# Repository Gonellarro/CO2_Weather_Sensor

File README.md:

# README - SENSOR DE CO2

Este documento describe como realizar un dispositivo de bajo costo para registrar la cantidad de CO2 que hay en el aire, indicando mediante un semáforo en que situación nos encontramos. Se incluyen dos versiones de programa en función de si necesitamos solo un avisador de CO2 máximo o si queremos llevar un control de aire, temperatura y humedad más sofisticado y centralizado mediante la consola de Grafana.

----------

TIEMPO ESTIMADO: **120/240 min (básico/avanzado)**

-------

**APRENDERÁS:**

```
IDE ARDUINO, I2C, COMUNICACIÓN SERIE, INCLUSIÓN DE LIBRERÍAS, INCORPORACIÓN DE PLACAS, WIFI, DOCKER, INFLUXDB, TELEGRAPH, GRAFANA, MQTT, SENSORES
```

------

## Visión general

El año 2020 nos sorprendió a todos con la llegada de un virus devastador que ha infectado a todo el mundo sin distinción de raza, sexo o credo. Las fronteras políticas y geográficas han sido meras entelequias humanas que este virus ha despreciado y no le han parado en su expansión. 

La humanidad se ha visto amenazada de forma inesperada y con una rapidez no vista en mucho tiempo. Solo los confinamientos masivos por parte de las naciones han conseguido contener o mitigar el avance del mismo, siendo las otras alternativas, mucho menos efectivas. La dualidad entre el mantenimiento de la economía y la preservación de la salud de la población es el tema que más preocupa a los dirigentes del mundo, ya que este se debate entre salvaguardar nuestra salud o la economía. Muchas de las voces autorizadas del mundo, comparan la reciente situación como mucho peor a la reciente segunda guerra mundial y poder mantener el tejido productivo en marcha sorteando los contagios es el reto que nos tiene en marcha durante el final del 2020 principios del 2021. Hasta que el mundo entero no se inmunice mediante el uso de vacunas o la reversión del virus, tenemos que ser capaces de buscar formas o soluciones que nos ayuden a protegernos y mantener como se pueda la actividad económica. 

Es por eso, que científicos de todo el mundo han considerado la relación entre la ventilación y  la transmisión del virus como una parte fundamental en la expansión del mismo. Un espacio mal o poco ventilado con infectados por el virus es la causa más habitual de contagio. Los aerosoles han aparecido como vectores muy eficaces en la transmisión y es por ello, que para poder controlar estos aerosoles en el aire se apuesta por sensores de CO2 que nos indican, no si existen aerosoles, sino cuan viciado está el aire. La relación entre cantidad de CO2 y dichos aerosoles es directa, con lo cual no es necesario medir niveles de COVID o aerosoles, sino de CO2 y nos aseguraremos un aire limpio sin costes elevados.

Este proyecto trata de obtener lecturas de varios sensores (de CO2, temperatura y humedad) para indicar la calidad del aire en función del CO2. El controlador que se encarga de ello se trata de un Wemos D1 Mini que es un microcontrolador pequeño, barato y con Wifi, que nos permitirá recoger los datos necesarios y enseñarlos mediante un semáforo de colores e incluso, si disponemos de red Wifi, mediante una pequeña página web. El sensor que utilizamos para registrar las ppm (partes por millón) de CO2 es el MHZ19b que hemos comprobado que tiene una fiabilidad y precisión bastante elevada junto con un precio acceptable. El sensor de humedad es el BME280 que también da lecturas de temperatura, pero estas son menos rigurosas. Se tomarán estas últimas de forma cuantitativa y no cualitativa.

El proyecto tiene una segunda parte, más elaborada y compleja, que pretende realizar un sistema de control centralizado de los datos que toma el microcontrolador, usando bases de datos y el sistema gestor de gráficas y dashboards, llamado Grafana. Todo este sistema, se puede instalar sobre un PC, una máquina virtual, una raspberry, etc... pero para hacerlo mucho más modular y portable, se ha optado por hacerlo mediante docker-compose que permite replicarlo con muy poco esfuerzo.

> **Nota:** Sea cual sea el nivel de integración que se quiera llevar a cabo (básico o avanzado), el proyecto se ha pensado para que se pueda llevar a cabo sin cambios. Esto significa que tanto los dispositivos, montaje como código, son los mismos en el nivel básico y el avanzado. Desde un principio se ha pensado en poderlo llevar a cabo sin más pretensión que el nivel básico y no penaliza a aquellos que no quieran complicarse la vida o no necesiten tanto nivel de monitorización

## Dispositivo

El dispositivo básico registrará los datos de CO2, temperatura y humedad de los sensores que incorpora.  Una vez montado el circuito, cargado el programa al Wemos y dado corriente, este empezará con un proceso de precalentado (3 minutos en los que los 3 leds parpadearán de forma secuencial) y se encenderá el led que corresponda al nivel de CO2.

### Componentes necesarios

-  1 x Wemos D1 Mini
-  3 x Resistencias 220 Ohm
-  3 x Led (Rojo, Naranja y Verde)
-  1 x MHZ19B
-  1 x BME 280
-  1 x Protoboard/PCB
-  1 x Cable USB
-  1 x Fuente alimentación 5V/1A

### Diagrama esquemático

### Construir el circuito

A la hora de construir el circuito debemos de tener en cuenta todo el patillaje y como está conectado entre ellos. Es importante tener una descripción detallada de cada componente, así como su DataSheet si es necesario. Veamos ahora el patillaje de cada componente:

- *Wemos D1 mini pinout*

- *MHZ19 pinout*

- *BME280 pinout* 

- *LEDs pinout (recordar que son diodos y por tanto, tienen una pata + y la otra -)*

Procederemos al montaje del circuito en una protoboard, tal y como se muestra en el diagrama esquemático y respetando los pines del diagrama. Hay que conectar el Wemos al ordenador mediante un cable USB, que será el que nos permitirá darle corriente por una parte y cargar el programa por otra.

> **Nota**: Deberemos comprobar en el IDE de Arduino en la sección que viene, que la placa ha sido conectada en un puerto del PC mediante la revisión del puerto. Si no es así, hay que revisar las conexiones con el Wemos, el cable o cambiar de conexión USB del PC, teniendo en cuenta que cada conexión corresponde a un COM diferente.

### Creación del código: Detectar niveles de CO2 con LEDS

1. **Importación de la placa Wemos D1 mini**

Lo primero que debemos hacer al abrir el Arduino IDE es importar los microcontroladores que queremos que sea capaz de compilar. Para ello, añadiremos la linea

```
http://arduino.esp8266.com/stable/package_esp8266com_index.json
```

a las preferencias del IDE/Gestión de URLs adicionales de tarjetas:

Podemos ver que lo hemos importado bien si encontramos la placa LOLIN(WEMOS) D1 R2 & mini en el menú Herramientas\Gestor de tarjetas\ESP8266 Boards (2.7.4) .

Si hemos conectado correctamente el Wemos, lo veremos conecado en el menú Herramientas\Puerto

2. **Importación de las librerías del sensor de CO2**

Debemos bajarnos el ZIP de la librería que está en https://github.com/strange-v/MHZ19 e importarlo como librería. 

Vamos al menú Programa\Incluir Librería\Añadir biblioteca .ZIP

Podemos comprobar que está bien si encontramos la librería en el menú Programa\Incluir Librería\MHZ19

3. **Importación de las librerías del sensor de temperatura**

En este caso es más sencillo, ya que tenemos que añadir solo las librerías de Adafruit y que ya están listadas por defecto. Vamos al menú Programa\Incluir Librería\Administrar bibliotecas y buscamos por BME. Elegimos la librería de Adafruit

Igualmente comprobaremos que lo hemos cargado correctamente si aparece dentro de las librerías disponibles.

4. **El código**

Una vez ya tenemos todo el sistema preparado, podemos cargar el código. Para tener una estructura más clara, legible y escalable, se ha dividido en 5 ficheros diferentes:

- MHZ19B_wemos_BM280.1.3.ino
- Config.h
- Wifi_credentials.h
- CO2_thershold.h
- MQTT.h

El fichero principal, que controla todo el proceso (MHZ19B_wemos_BM280.1.3.ino)

```python
// Wemos MH-Z19B BME28
// Meassure CO2 and environmental data with Wemos D1 mini, MH-Z19B i BME280
//
// Martí Vich, 01/12/2020
//
// based on / credits to:
// https://github.com/AndreasIBZ/ESP32/tree/main/CCS811_BME280_influxDB_Makespace_Mallorca
// https://github.com/miguelangelcasanova/codos
// https://github.com/Makespace-Mallorca/codos

//
// ##### TODO #####
// - Revisión si se puede optimizar el código
// - Revisión del Deep Sleep
// - Mover a libreria parte del código que sea modulable

// #####################################################################################
//
// Code description
// - Measurement of CO2 level and temperature using the MH-Z19B
// - Measurement of the environment (temperature, pressure, humidity) using the BME280
// - Signage of CO2 levels Acceptable, Warning  and Dangerous 
//
// Wiring MH-Z19B -> Wemos D1 mini
// Vin - 5V (VIN)
// RX - GPIO 13 (Software Serial TX) - D8
// TX - GPIO 15 (Software Serial RX) - D7
// GND - GND
//

//
// Wiring BME280 -> Wemos D1 mini
// SCL - D1
// SDA - D2
// VCC - 3V3
// GND - GND

//
// Traffic Light
// GREEN  - D4
// ORANGE - D5
// RED    - D6

// Changelog
// 01/12/2020 - Primera versió 
// 02/12/2020 - Afegim el semàfor i el sensor BME280 
// 03/12/2020 - Revisió rutina d'espera per poder accedir millor al servidor web
//            - Afegit fitxer Wifi_credentials.h
//            - Afegit fitxer CO2_thershold.h
//            - Afegit fitxer Config.h
// 22/12/2020 - Afegit codi MQTT
//            - Revisat codi anterior
//
// #########################################################################################
//
// MH-Z19B
#include <SoftwareSerial.h> // Click here to get the library: http://librarymanager/All#EspSoftwareSerial
#include <MHZ19.h> // library for MH-Z19B: https://github.com/strange-v/MHZ19
#include "CO2_thershold.h" // Límits pels llindars de CO2
#define TXPin 15 // D8 - para MH-Z19B
#define RXPin 13 // D7 - para MH-Z19B

// Instantiate SoftwareSerial
SoftwareSerial ss(RXPin, TXPin);// RX, TX
// Instantiate the MH-Z19B CO2-Sensor with SoftwareSerial
MHZ19 mhz(&ss); 

float CO2;
float Mtemperature;

// BME280
#include <Wire.h>
#include <Adafruit_Sensor.h>
#include <Adafruit_BME280.h>

#define SEALEVELPRESSURE_HPA (1013.25)
// Instantiate the BME sensor with I2C
Adafruit_BME280 bme; 
float Btemperature, Bhumidity, Bpressure, Baltitude;

// WebServer
#include <ESP8266WebServer.h>
#include "WiFi_credentials.h" // credenciales del WiFi
// Instantiate WebServer at port 80
ESP8266WebServer server(80);  

// Traffic Light
int green = 2;   //D4
int yellow = 14; //D5
int red = 12;    //D6

//MQTT
#include <ESP8266WiFi.h>
#include <PubSubClient.h>
#include "MQTT.h" // Confifguració MQTT

//Buffer to decode MQTT messages
char message_buff[100];

long lastMsg = 0;   
long lastRecu = 0;
bool debug = false;  //Display log message if True

WiFiClient espClient;
PubSubClient client(espClient);

// Configuracions generals 
#include "Config.h" // Configuracions generals

// Control del tiempo
long timerCount = 0;

void setup_wifi()
{
  delay(10);
  Serial.println("------------------WIFI---------------");
  Serial.println("Connecting to ");
  Serial.println(WIFI_NAME);

  //connect to your local wi-fi network
  WiFi.begin(WIFI_NAME, WIFI_PASS);

  //check wi-fi is connected to wi-fi network
  while (WiFi.status() != WL_CONNECTED) {
  delay(1000);
  Serial.print(".");
  }
  Serial.println("");
  Serial.println("WiFi connected..!");
  Serial.print("Got IP: ");  Serial.println(WiFi.localIP());

  server.on("/", handle_OnConnect);
  server.onNotFound(handle_NotFound);

  server.begin();
  Serial.println("HTTP server started");
}

void setup()
{
  Serial.begin(115200);
  //WIFI connection
  setup_wifi();

  //MQTT
  client.setServer(mqtt_server, 1883);    // Configure MQTT connexion
    
  //Initialize traffic light
  pinMode(green, OUTPUT);
  pinMode(yellow, OUTPUT);
  pinMode(red, OUTPUT);

  //BME280
  Serial.println("-- Initializing BME280...");
  bme.begin(0x76); 

  // MH-Z19B: Initialize Software Serial
  Serial.println("-- Initializing SoftwareSerial (MH-Z19B)...");
  { ss.begin(9600); 
      delay(100);
      mhz.setAutoCalibration( false );  // default settings - off autocalibration
      Serial.println("Preheating...");
      //Preheating of the sensor (usually 3 minutes)
      for (int i = 0; i<3; i++){
        for (int j = 0; j< int(preheating_Time/(3000)) ; j++){          
          digitalWrite(red, LOW);
          digitalWrite(yellow, LOW);
          digitalWrite(green, LOW);
          delay(int(500));
          if (i==0){
            digitalWrite(red, HIGH);

          }
          if (i==1){
            digitalWrite(red, LOW);  
            digitalWrite(yellow, HIGH);          
         
          }
          if (i==2){
            digitalWrite(red, LOW);  
            digitalWrite(yellow, LOW);   
            digitalWrite(green, HIGH);       
         
          }
          delay(500);          
        }
      }
      Serial.println("-- Reading MH-Z19B --");
      delay(200);
      Serial.print( "Acuracy:" ); 
      Serial.println(mhz.getAccuracy()? "ON" : "OFF" );
      Serial.print( "Detection Range: " ); 
      Serial.println( 5000 );

  }  
}

//Reconnexion MQTT
void reconnect() {
  // Loop until we're reconnected
  int intents = 0;
  while (!client.connected() && intents < 5) {
    Serial.print("Connecting to MQTT broker ...");
    if (client.connect("ESP8266Client", mqtt_user, mqtt_password)) {
      Serial.println("Connected to MQTT Server");
    } else {
      Serial.print("Failed to connect to MQTT server, error : ");
      Serial.print(client.state());
      Serial.println(" Wait 5 secondes before to retry");
      delay(5000);
      intents = intents + 1;
    }
  }
}

void loop()
{
  // Grabbing data from MHZ19B sensor
  MHZ19_RESULT response = mhz.retrieveData();
  if (response == MHZ19_RESULT_OK)
  {
    CO2 = mhz.getCO2();
    Mtemperature = mhz.getTemperature();    
    //Serial.print("MZH19B - ");
    //Serial.print(F("CO2: "));
    //Serial.println(CO2);
    //Serial.print(F("Min CO2: "));
    //Serial.println(mhz.getMinCO2());
    //Serial.print("MZH19B - ");
    //Serial.print(F("Temperature: "));
    //Serial.print(Mtemperature);
    //Serial.print(F("Accuracy: "));
    //Serial.println(mhz.getAccuracy());
  }
  else
  {
    Serial.print(F("MHZ Error, code: "));
    Serial.println(response);
  }
  // Switch CO2
  if (CO2 < CO2_med) {
    digitalWrite(green, HIGH);
    digitalWrite(yellow, LOW);
    digitalWrite(red, LOW);
    
  }
  else{
    if (CO2 > CO2_max) {
       digitalWrite(red, HIGH);
       digitalWrite(yellow, LOW);
       digitalWrite(green, LOW);
    }
    else{
       digitalWrite(yellow, HIGH);
       digitalWrite(green, LOW);
       digitalWrite(red, LOW);
    }    
  }

  // Grabbing data from BME280
  Btemperature = bme.readTemperature();
  Bhumidity = bme.readHumidity();
  Bpressure = bme.readPressure() / 100.0F;
  Baltitude = bme.readAltitude(SEALEVELPRESSURE_HPA);

  //Changin format of data to be sending via Web && MQTT
  String t = String(Btemperature);
  String tM  = String(Mtemperature);
  String h = String(Bhumidity);
  String p = String(Bpressure);
  String a = String(Baltitude);
  String c = String(CO2);

  //Serial.print(F("BME280 - "));
  //Serial.println("Temperature: " + t);

  //MQTT
  if (!client.connected()) {
    reconnect();
  }
  client.loop();    
  delay(500);  

  // Wifi server && MQTT Sending data
  // 1st record the time from the timer
  timerCount = millis();
   while (millis() < timerCount + delay_Time) {
    //Wifi server
    server.handleClient();
    //MQTT
    //Enviam cada minut les messures preses
    if (timerCount - lastMsg > 1000*tMostreig){

      lastMsg = timerCount;
    
      Serial.print("BME280 - ");
      Serial.println("Humidity: " + h);
      Serial.print("MZH19B - ");
      Serial.println("CO2: " + c);
      Serial.println("Temperature: " + tM);
              
      client.publish(String(temperature_topic).c_str(), String(tM).c_str(), true);   // Publish temperature on temperature_topic
      client.publish(String(humidity_topic).c_str(), String(h).c_str(), true);       // and humidity
      client.publish(String(co2_topic).c_str(), String(c).c_str(), true);            // and CO2      
      
    }
    
    //He de revisar que fa això
    //if (now - lastRecu > 100 ) {
    //  lastRecu = now;
    //  client.subscribe("homeassistant/switch1");
    //}

   }

}

void handle_OnConnect() {
  Btemperature = bme.readTemperature();
  Bhumidity = bme.readHumidity();
  Bpressure = bme.readPressure() / 100.0F;
  Baltitude = bme.readAltitude(SEALEVELPRESSURE_HPA);
  int CO2 = mhz.getCO2();
  float Mtemperature = mhz.getTemperature();
  server.send(200, "text/html", SendHTML(Btemperature,Mtemperature,Bhumidity,Bpressure,Baltitude, CO2)); 
  //String t = String(Btemperature);
  Serial.println("Connection done!");
}

void handle_NotFound(){
  server.send(404, "text/plain", "Not found");
}

String SendHTML(float Btemperature,float Mtemperature,float humidity,float pressure,float altitude, int CO2){
  String ptr = "<!DOCTYPE html> <html>\n";
  ptr +="<head><meta name=\"viewport\" content=\"width=device-width, initial-scale=1.0, user-scalable=no\">\n";
  ptr +="<title>ESP8266 Weather Station</title>\n";
  ptr +="<style>html { font-family: Helvetica; display: inline-block; margin: 0px auto; text-align: center;}\n";
  ptr +="body{margin-top: 50px;} h1 {color: #444444;margin: 50px auto 30px;}\n";
  ptr +="p {font-size: 24px;color: #444444;margin-bottom: 10px;}\n";
  ptr +="</style>\n";
  ptr +="</head>\n";
  ptr +="<body>\n";
  ptr +="<div id=\"webpage\">\n";
  ptr +="<h1>ESP8266 Weather Station</h1>\n";
  ptr +="<p>Temperature (BME): ";
  ptr +=Btemperature;
  ptr +="<p>Temperature (MHZ): ";
  ptr +=Mtemperature;  
  ptr +="&deg;C</p>";
  ptr +="<p>Humidity: ";
  ptr +=humidity;
  ptr +="%</p>";
  ptr +="<p>Pressure: ";
  ptr +=pressure;
  ptr +="hPa</p>";
  ptr +="<p>Altitude: ";
  ptr +=altitude;
  ptr +="m</p>";
  ptr +="<p>CO2: ";
  ptr +=CO2;
  ptr +="ppm</p>";
  ptr +="</div>\n";
  ptr +="</body>\n";
  ptr +="</html>\n";
  return ptr;
}
```

Explicación del código paso a paso:

Inicialización del sensor de CO2 (MHZ19B): Este sensor permite la captura de datos mediante transmisión serie. Creamos un objeto de la clase *SoftwareSerial* y lo llamamos *ss*. Le asignamos lis pines 15 y 13 del Wemos para la transmisión y recepción de los datos del sensor. Ver datasheet para más detalles. Creamos un objeto de tipo *MHZ19* llamado *mhz* al cual le asignamos como canal de transmisión serie el objeto que hemos creado *ss*. 

Finalmente, creamos las variables *CO2* y *Mtemperature* que nos guardaran estos valores del sensor.

```python
// MH-Z19B
#include <SoftwareSerial.h> // Click here to get the library: http://librarymanager/All#EspSoftwareSerial
#include <MHZ19.h> // library for MH-Z19B: https://github.com/strange-v/MHZ19
#include "CO2_thershold.h" // Límits pels llindars de CO2
#define TXPin 15 // D8 - para MH-Z19B
#define RXPin 13 // D7 - para MH-Z19B

// Instantiate SoftwareSerial
SoftwareSerial ss(RXPin, TXPin);// RX, TX
// Instantiate the MH-Z19B CO2-Sensor with SoftwareSerial
MHZ19 mhz(&ss); 

float CO2;
float Mtemperature;
```

Veamos ahora el sensor de presión, el BME280. Cargamos las librerías correspondientes para poder interactuar con él y ya lo instanciamos para poder trabajar mediente el protocolo [I2C](https://www.i2c-bus.org/):

```python
// BME280
#include <Wire.h>
#include <Adafruit_Sensor.h>
#include <Adafruit_BME280.h>

#define SEALEVELPRESSURE_HPA (1013.25)
// Instantiate the BME sensor with I2C
Adafruit_BME280 bme; 
float Btemperature, Bhumidity, Bpressure, Baltitude;

```

Seguimos con la creación del servidor web. Para ello cargamos las librerías necesarias, cargamos las credenciales del fichero externo *Wifi_credentials.h* y creamos el objeto *server* en el puerto 80 de tipo *ESP8266Webserver*.

```
// WebServer
#include <ESP8266WebServer.h>
#include "WiFi_credentials.h" // credenciales del WiFi
// Instantiate WebServer at port 80
ESP8266WebServer server(80);  
```

Asignamos los pines 2, 12 y 14 para los leds del semáforo.

```python
// Traffic Light
int green = 2;   //D4
int yellow = 14; //D5
int red = 12;    //D6
```

Finalmente cargamos el módulo MQTT para enviar los mensajes al servidor MQTT. Se crea un cliente de wifi para poder interactuar con el servidor MQTT (espClient) y el objeto client de tipo PubSubClient para publicar las medidas mediante el cliente wifi espClient.

```python
//MQTT
#include <ESP8266WiFi.h>
#include <PubSubClient.h>
#include "MQTT.h" // Confifguració MQTT

//Buffer to decode MQTT messages
char message_buff[100];

long lastMsg = 0;   
long lastRecu = 0;
bool debug = false;  //Display log message if True

WiFiClient espClient;
PubSubClient client(espClient);
```

Creamos la función de setup de la Wifi. Mostramos por el monitor serie cual esla  IP que le ha dado el servidor de DHCP. Si queremos que use una IP estática hay que cambiar esta parte del código.

También arranca el servidor web cuando ya tiene IP.

```python
void setup_wifi()
{
  delay(10);
  Serial.println("------------------WIFI---------------");
  Serial.println("Connecting to ");
  Serial.println(WIFI_NAME);

  //connect to your local wi-fi network
  WiFi.begin(WIFI_NAME, WIFI_PASS);

  //check wi-fi is connected to wi-fi network
  while (WiFi.status() != WL_CONNECTED) {
  delay(1000);
  Serial.print(".");
  }
  Serial.println("");
  Serial.println("WiFi connected..!");
  Serial.print("Got IP: ");  Serial.println(WiFi.localIP());

  server.on("/", handle_OnConnect);
  server.onNotFound(handle_NotFound);

  server.begin();
  Serial.println("HTTP server started");
}
```

Analizamos el setup más despacio para revisar que hace cada parte:

1. Indicamos la velocidad de conexión, arrancamos la wifi, configuramos el cliente de MQTT con la dirección del servidor y el puerto, así como indicamos que los pines verde, naranja y rojo son de salida

```python
  Serial.begin(115200);
  //WIFI connection
  setup_wifi();

  //MQTT
  client.setServer(mqtt_server, 1883);    // Configure MQTT connexion
    
  //Initialize traffic light
  pinMode(green, OUTPUT);
  pinMode(yellow, OUTPUT);
  pinMode(red, OUTPUT);
```

2. Arrancamos la comunicación I2C con el BME280. Su dirección es la 0x76 (consultar datasheet)
3. Arrancamos la comunicación serie con el MHZ19B. Establecemos la velocidad de comunicación a 9600 baudios, realizamos el preheating como indican en el datasheet indicando mediante el parpadeo de los leds, que estamos precalentando el sensor. Van parpadeando uno a uno, durante un minuto, hasta que pasan los 3 minutos.

```python
  //BME280
  Serial.println("-- Initializing BME280...");
  bme.begin(0x76); 

  // MH-Z19B: Initialize Software Serial
  Serial.println("-- Initializing SoftwareSerial (MH-Z19B)...");
  { ss.begin(9600); 
      delay(100);
      mhz.setAutoCalibration( false );  // default settings - off autocalibration
      Serial.println("Preheating...");
      //Preheating of the sensor (usually 3 minutes)
      for (int i = 0; i<3; i++){
        for (int j = 0; j< int(preheating_Time/(3000)) ; j++){          
          digitalWrite(red, LOW);
          digitalWrite(yellow, LOW);
          digitalWrite(green, LOW);
          delay(int(500));
          if (i==0){
            digitalWrite(red, HIGH);          
      	  }
      	if (i==1){
        	digitalWrite(red, LOW);  
        	digitalWrite(yellow, HIGH);          
      	}
      	if (i==2){
        	digitalWrite(red, LOW);  
        	digitalWrite(yellow, LOW);   
        	digitalWrite(green, HIGH);            
      	}
      	delay(500);          
    	}
  	}
 	Serial.println("-- Reading MH-Z19B --");
  	delay(200);
  	Serial.print( "Acuracy:" ); 
  	Serial.println(mhz.getAccuracy()? "ON" : "OFF" );
  	Serial.print( "Detection Range: " ); 
  	Serial.println( 5000 );
```

Finalmente analizamos el loop, como parte más interesante de la práctica. 

1. Recogemos los datos de MHZ19B

```python
  // Grabbing data from MHZ19B sensor
  MHZ19_RESULT response = mhz.retrieveData();
  if (response == MHZ19_RESULT_OK)
  {
    CO2 = mhz.getCO2();
    Mtemperature = mhz.getTemperature();    
  }
  else
  {
    Serial.print(F("MHZ Error, code: "));
    Serial.println(response);
  }

```

2. Encendemos el led que toca en función del valor de CO2 obtenido. En este caso hemos optado por usar una secuencia de ifs anidados, pero se puede programar mediante la sentencia [switch...case](https://www.arduino.cc/reference/en/language/structure/control-structure/switchcase/)

```python
 // Switch CO2
  if (CO2 < CO2_med) {
    digitalWrite(green, HIGH);
    digitalWrite(yellow, LOW);
    digitalWrite(red, LOW);
    
  }
  else{
    if (CO2 > CO2_max) {
       digitalWrite(red, HIGH);
       digitalWrite(yellow, LOW);
       digitalWrite(green, LOW);
    }
    else{
       digitalWrite(yellow, HIGH);
       digitalWrite(green, LOW);
       digitalWrite(red, LOW);
    }    
  }

```

3. Recogemos los datos del BME280

```python
  // Grabbing data from BME280
  Btemperature = bme.readTemperature();
  Bhumidity = bme.readHumidity();
  Bpressure = bme.readPressure() / 100.0F;
  Baltitude = bme.readAltitude(SEALEVELPRESSURE_HPA);
```

4. Enviamos los datos por MQTT y lo publicamos al servidor web del Wemos

   Cada delay_time revisamos los datos

   ```python
     // Wifi server && MQTT Sending data
     // 1st record the time from the timer
     timerCount = millis();
      while (millis() < timerCount + delay_Time) {
   ```

   Atendemos el servicio web

   ```python
   //Wifi server
   server.handleClient();
   ```

   Cada minuto enviamos los datos al servicio de MQTT
   
   ```python
       //Enviam cada minut les messures preses
       if (timerCount - lastMsg > 1000*tMostreig){
   
       lastMsg = timerCount;
       
       Serial.print("BME280 - ");
       Serial.println("Humidity: " + h);
       Serial.print("MZH19B - ");
       Serial.println("CO2: " + c);
       Serial.println("Temperature: " + tM);
       
       client.publish(String(temperature_topic).c_str(), String(tM).c_str(), true);   // Publish temperature on temperature_topic
       client.publish(String(humidity_topic).c_str(), String(h).c_str(), true);       // and humidity
       client.publish(String(co2_topic).c_str(), String(c).c_str(), true);            // and CO2          
       }
   ```

El resto del código no es tan imprescindible para entender el funcionamiento del sensor y materializa lo que le hemos programado en lo explicado hasta aquí.

Revisamos el resto de ficheros:

Disponemos de un fichero de configuración general (config.h), que controla:

- Tiempo de preheating
- Tiempo de recarga de sensores
- Tiempo de muestreo de MQTT

```python
#ifndef Config_h

// General configuration parameters

const int delay_Time = 15000; // 15 seconds
const int preheating_Time = 180000; // 3 minutes
const int tMostreig = 15; // 60 seconds to send every meassurement to MQTT server

#endif  
```

Disponemos de un fichero (Wifi_credentials.h) que configura los parámetros de la wifi:

```python
#ifndef WiFi_credentials_h

// WiFi
const char WIFI_NAME[] = "your_ISD";
const char WIFI_PASS[] = "your_pass";

#endif
```

Disponemos de un fichero (CO2_thershold.h) que configura los umbrales de encendido de los leds:

```python
#ifndef CO2_thershold_h

// WiFi
const int CO2_med = 599;
const int CO2_max = 799;

#endif
```

Finalmente, disponemos de un fichero (MQTT.h) que configura los parámetros de los meassurements/topics que se envían mediante MQTT a la base de datos InfluxDB para visualizarlos en Grafana. Sin duda este es el fichero más extraño y no es necesario rellenar si no se van a usar los datos en un sistema centralizado.

```python
const char mqtt_server[] = "";   // MQTT Server IP address
const char mqtt_user[] = "";                // if exist
const char mqtt_password[] = "";            // idem

String device_name = "";

String temperature_topic = "sensors/" + device_name + "/temperature";  //Topic temperature
String humidity_topic = "sensors/" + device_name + "/humidity";        //Topic humidity
String co2_topic = "sensors/" + device_name + "/co2";                  //Topic CO2
```

### Pruebas y funcionamiento

Pasaremos ahora a cargar el código al Wemos. Para ello, una vez conectado el Wemos y confirmado que el IDE de Arduino lo detecta en algún puerto del PC, le daremos a compilar y subir.

Si todo ha ido bien, el programa se habrá compilado y se habrá subido al Wemos. Entonces veremos la secuencia de LEDs:

1. Led verde encendido: Búsqueda de Wifi y asignación de IP
2. Ciclo de encendido/apagado de cada uno de los leds durante un minuto, para precalentar el sensor de CO2 (primero el rojo, luego el naranja y finalmente el verde)
3. Finalemente se encenderá el Led correspondiente al nivel que le hayamos programado en el fichero de configuración.
4. Podemos acceder al dispositivo mediante Wifi a la dirección IP del mismo

//IMATGE

### BONUS: Creación de la placa PCB

Si queremos hacer el proyecto redondo, ya solo nos queda pasar todo el montaje a una placa. Podemos optar por las placas perforadas y cablear todos los componentes, o diseñar una placa desde cero y enviarla a fabricar. 

En este caso ya hemos realizado la placa, la hemos diseñado con [Kicad](https://kicad.org/) y enviado a fabricar a un proveedor de Internet. Dejamos los ficheros necesarios (JLCPCB.zip) en la carpeta  *Dessign/Kicad* para que se puedan enviar al proveedor que se desee y poder acabar el dispositivo de forma que se pueda usar en la vida real.

El dispositivo montado

--------

## Monitorización

Ya tenemos el dispositivo montado y funcionando. Ahora queremos poder monitorizar de forma centralizada los datos que registra: CO2, temperatura, humedad y presión. Si bien hay que hacer notar, los datos de la concentración de CO2 parecen bastante reales y acertados, tanto los de temperatura como de presión salen fuera de margen y solo se pueden tomar de forma cuantitativa y no cualitativa.

Ejemplo de dashboard de monitorización, que es a lo que aspiramos en este punto:

### Arquitectura

---------

- Por una parte, el dispositivo tiene la capacidad de poder conectarse a una red IP mediante WIFI pero debemos evitar que se pueda conectar con Internet. <u>Solamente debe de ser accesible dentro de la red local</u>. Esto lo hace más seguro y  tenemos el sistema menos expuesto a posibles ataques externos. Por tanto, pongo como premisa que el dispositivo (Wemos D1 mini) no esté conectado a una red externa. Esto no tiene que ver que no se pueda monitorizar desde el exterior, ojo. Lo que hay que evitar a toda costa es que nuestro dispositivo pueda ser accesible.

- Los datos obtenidos deben de incorporarse en una base de datos local para poderlos gestionar de una forma adecuada.

- Mediante un navegador web accedemos a la base de datos y obtenemos las gráficas que la aplicación web que elijamos nos muestre desde nuestra red local.

  > **Nota**: Si queremos que sea accesible desde Internet, podemos poner un proxy reverso, pero no es el objetivo de esta práctica. Si se quiere realizar, recomendamos el docker *jwilder/nginx-proxy*.

Una vez clara cual va a ser la arquitectura, debemos elegir que componentes usar. Debe de quedar claro que esta es una posible elección y que el mercado ofrece muchas soluciones tanto gratuitas como de pago y no necesariamente deberíamos hacerlo así. Es simplemente la que nos ha parecido que cubría mejor las necesidades del proyecto. 

- **Máquina usada:** Máquina Virtual Ubuntu Server 20.04 (2GB de RAM, Core i3 7100) pero se puede usar una raspberry pi, una máquina dedicada o un servicio cloud
- **Container:** docker-compose. 
- **Servicio de monitorización:**  Grafana
- **Base de datos:** InfluxDB
- **Listener:**
  - Mosquito MQTT
  - Telegraf

A esta configuración se le conoce como el stack TIG (Telegraf, InfluxDB y Grafana) con lo que encontraremos bastante información en Internet sobre ello si queremos indagar un poco más. El funcionamiento práctico es el siguiente:

*Fuente: https://hackmd.io/@lnu-iot/tig-stack*

Si juntamos MQTT con mosquito y TIG: 

*Fuente: https://dzone.com/articles/raspberry-pi-iot-sensors-influxdb-mqtt-and-grafana*

#### Instalación

----------------

1. **Instalar docker**: Ver [documentación](https://docs.docker.com/engine/install/ubuntu/) de docker para Ubuntu. En la misma página encontraremos como instalarlo en otros sistemas operativos.

   ***Resumen de comandos:***

   Actualizamos y confirmamos que tenemos todos los paquetes para poder usar apt sobre un repositorio HTTPS:

   ```bash
   $ sudo apt-get update
   
   $ sudo apt-get install \
       apt-transport-https \
       ca-certificates \
       curl \
       gnupg-agent \
       software-properties-common
   ```

   Añadimos la clave GPG oficial de Docker:

   ```bash
   $ curl -fsSL https://download.docker.com/linux/ubuntu/gpg | sudo apt-key add -
   ```

   Añadimos el repositorio **estable**

   ```bash
   $ sudo add-apt-repository \
      "deb [arch=amd64] https://download.docker.com/linux/ubuntu \
      $(lsb_release -cs) \
      stable"
   ```

   Finalmente instalamos el motor de Docker:

   ```bash
    $ sudo apt-get update
    $ sudo apt-get install docker-ce docker-ce-cli containerd.io
   ```

   Verificamos que la instalación de Docker Engine está funcionando correctamente arrancando la imagen *hello-world*

   ```bash
   $ sudo docker run hello-world
   ```

   Si va bien, nos saldrá una pantalla como esta:

2. **Instalar docker-compose:** Para ello seguimos la documentación oficial de docker que podemos encontrar [aquí](https://docs.docker.com/compose/install/). Aunque está alojada en Github, la misma página de docker tiene un manual muy completo y es el que hemos seguido.

   ***Resumen de comandos:***

   Descarga de la última versión estable de docker-compose:

   ```bash
   sudo curl -L "https://github.com/docker/compose/releases/download/1.28.2/docker-compose-$(uname -s)-$(uname -m)" -o /usr/local/bin/docker-compose
   ```

   Añadimos los permisos de ejecución al binario:

   ```bash
   sudo chmod +x /usr/local/bin/docker-compose
   ```

   Comprobamos que la instalación ha sido correcta ejecutando el comando:

   ```bash
   docker-compose --version
   ```

   Si ha ido bien debemos obtener un mensaje como este:

#### Configuración

------------

Ahora ya tenemos la base instalada para poder correr los servicios necesarios. Repasemos el montaje:

**MQTT:** El dispositivo debe enviar las medidas mediante un cliente MQTT a un servidor MQTT.  Debe de estar configurado tanto para recibir los datos del dispositivo como para enviarlos a la base de datos. Veamos quedaría en la configuración de *docker-compose*:

```yaml
  mqtt:
    container_name: mqtt
    image: eclipse-mosquitto:latest
    networks:
      - tig_net    
    ports:
      - "1883:1883"
      - "9001:9001"
    user: "0"
    volumes:
      - mosquitto_volume:/mosquitto
    restart: always
```

***Puntos importantes***

```
- puertos de escucha de los dispositivos: 1883
- puerto de escucha web: 9001
- definimos la red para este stack
```

*Info de la imagen: https://hub.docker.com/_/eclipse-mosquitto*

**TELEGRAF:** El servidor MQTT no es capaz de transferir los datos directamente a la base de datos y necesita un servicio de escucha que los pase en el formato correcto de la base de datos elegida, en este caso, InfluxDB. El programa para traducirlo es el Telegraf. Su configuración se divide en 2 partes: *docker-compose* y un fichero de configuración (Telegraf sirve para recolectar información de muy diversas fuentes y consolidarlas a otras muy diversas bases de datos/componentes). 

docker-compose:

```yaml
  telegraf:
    container_name: telegraf
    image: telegraf
    networks:
      - tig_net    
    volumes:
      - ./tig/config/telegraf:/etc/telegraf:ro
      - /var/run/docker.sock:/var/run/docker.sock
    restart: always
    depends_on:
      - influxdb
      - mqtt
```

Fichero de configuración: Este fichero hay que crearlo y guardarlo en la ubicación *dc_tig/tig/conf/telegraf/telegraf.conf* :

*Parte MQTT*

```bash
 [[inputs.mqtt_consumer]]
#   ## Broker URLs for the MQTT server or cluster.  To connect to multiple
#   ## clusters or standalone servers, use a seperate plugin instance.
#   ##   example: servers = ["tcp://localhost:1883"]
#   ##            servers = ["ssl://localhost:1883"]
#   ##            servers = ["ws://localhost:1883"]
   servers = ["tcp://mqtt:1883"]
#
#   ## Topics that will be subscribed to.
   topics = [
     "telegraf/host01/cpu",
     "telegraf/+/mem",
     "sensors/#"
   ]
#
#   ## The message topic will be stored in a tag specified by this value.  If set
#   ## to the empty string no topic tag will be created.
#   # topic_tag = "topic"
#
#   ## QoS policy for messages
#   ##   0 = at most once
#   ##   1 = at least once
#   ##   2 = exactly once
#   ##
#   ## When using a QoS of 1 or 2, you should enable persistent_session to allow
#   ## resuming unacknowledged messages.
    qos = 0
#
#   ## Connection timeout for initial connection in seconds
#   # connection_timeout = "30s"
#
#   ## Maximum messages to read from the broker that have not been written by an
#   ## output.  For best throughput set based on the number of metrics within
#   ## each message and the size of the output's metric_batch_size.
#   ##
#   ## For example, if each message from the queue contains 10 metrics and the
#   ## output metric_batch_size is 1000, setting this to 100 will ensure that a
#   ## full batch is collected and the write is triggered immediately without
#   ## waiting until the next flush_interval.
#   # max_undelivered_messages = 1000
#
#   ## Persistent session disables clearing of the client session on connection.
#   ## In order for this option to work you must also set client_id to identify
#   ## the client.  To receive messages that arrived while the client is offline,
#   ## also set the qos option to 1 or 2 and don't forget to also set the QoS when
#   ## publishing.
#   # persistent_session = false
#
#   ## If unset, a random client ID will be generated.
#   # client_id = ""
#
#   ## Username and password to connect MQTT server.
    username = "telegraf"
    password = "telegraf"
#
#   ## Optional TLS Config
#   # tls_ca = "/etc/telegraf/ca.pem"
#   # tls_cert = "/etc/telegraf/cert.pem"
#   # tls_key = "/etc/telegraf/key.pem"
#   ## Use TLS but skip chain & host verification
#   # insecure_skip_verify = false
#
#   ## Data format to consume.
#   ## Each data format has its own unique set of configuration options, read
#   ## more about them here:
#   ## https://github.com/influxdata/telegraf/blob/master/docs/DATA_FORMATS_INPUT.md
    #data_format = "influx"
    data_format = "value"
    data_type = "float"
```

***Puntos importantes:***

```
- servidor:  tcp://mqtt:1883. Hay que tener en cuenta que el servicio de docker-compose crea una red privada con los nombres de los "servicios" definidos en el fichero yml. El nombre que le pongamos al servicio de mqtt debe de ser el que pongamos aquí como servidor. 

- topics: aquí hay que definir los topics que queremos que escuche/publique el servidor MQTT

- username/password: deberemos de configurar el servicio con un usuario y contraseña en el fichero yml. Estos datos son los que pondremos aquí.

- data_format: el formato de datos es importante. Reconozco que es el punto en que más fallo porque no lo tengo muy claro. He probado influx y he tendio problemas, con lo que he optado por estos, pero no lo tengo muy claro que deba de ser así.
```

*Parte InfluxDB*

```yaml
[[outputs.influxdb]]
  ## The full HTTP or UDP URL for your InfluxDB instance.
  ##
  ## Multiple URLs can be specified for a single cluster, only ONE of the
  ## urls will be written to each interval.
  # urls = ["unix:///var/run/influxdb.sock"]
  # urls = ["udp://127.0.0.1:8089"]
   urls = ["http://influxdb:8086"]

  ## The target database for metrics; will be created as needed.
  ## For UDP url endpoint database needs to be configured on server side.
   database = "telegraf"

  ## The value of this tag will be used to determine the database.  If this
  ## tag is not set the 'database' option is used as the default.
  # database_tag = ""

  ## If true, the 'database_tag' will not be included in the written metric.
  # exclude_database_tag = false

  ## If true, no CREATE DATABASE queries will be sent.  Set to true when using
  ## Telegraf with a user without permissions to create databases or when the
  ## database already exists.
   skip_database_creation = false

  ## Name of existing retention policy to write to.  Empty string writes to
  ## the default retention policy.  Only takes effect when using HTTP.
   retention_policy = ""

  ## The value of this tag will be used to determine the retention policy.  If this
  ## tag is not set the 'retention_policy' option is used as the default.
  # retention_policy_tag = ""

  ## If true, the 'retention_policy_tag' will not be included in the written metric.
  # exclude_retention_policy_tag = false

  ## Write consistency (clusters only), can be: "any", "one", "quorum", "all".
  ## Only takes effect when using HTTP.
  # write_consistency = "any"

  ## Timeout for HTTP messages.
  # timeout = "5s"

  ## HTTP Basic Auth
   username = "telegraf"
   password = "telegraf"

  ## HTTP User-Agent
  # user_agent = "telegraf"

  ## UDP payload size is the maximum packet size to send.
  # udp_payload = "512B"

  ## Optional TLS Config for use on HTTP connections.
  # tls_ca = "/etc/telegraf/ca.pem"
  # tls_cert = "/etc/telegraf/cert.pem"
  # tls_key = "/etc/telegraf/key.pem"
  ## Use TLS but skip chain & host verification
  # insecure_skip_verify = false

  ## HTTP Proxy override, if unset values the standard proxy environment
  ## variables are consulted to determine which proxy, if any, should be used.
  # http_proxy = "http://corporate.proxy:3128"

  ## Additional HTTP headers
  # http_headers = {"X-Special-Header" = "Special-Value"}

  ## HTTP Content-Encoding for write request body, can be set to "gzip" to
  ## compress body or "identity" to apply no encoding.
  # content_encoding = "gzip"

  ## When true, Telegraf will output unsigned integers as unsigned values,
  ## i.e.: "42u".  You will need a version of InfluxDB supporting unsigned
  ## integer values.  Enabling this option will result in field type errors if
  ## existing data has been written.
  # influx_uint_support = false

```

***Puntos importantes:***

```
- urls: Igual que en el caso anterior, debemos de indicar el nombre del servidor que corresponde con el de la imagen que hemos configurado en el fichero yml.

- database: debe de ser la BD que creamos en el servicio de InfluxDB 

- user/password: los que se indican en el servicio de InfluxDB
```

*Info sobre la imagen https://hub.docker.com/_/telegraf*

**INFLUXDB:** Esta es la parte de la base de datos. Esta debe almacenar los datos del dispositivo. En el caso de Influx se tratan como medidas o *meassures*. La parte de configuración del fichero docker-compose es esta:

```yaml
  influxdb:
    container_name: influxdb
    image: influxdb
    networks:
   		- tig_net    
    ports:
        - "8086:8086"
    volumes:
        - ./tig/data/influxdb:/var/lib/influxdb
    environment:
      - INFLUXDB_DB=telegraf
      - INFLUXDB_ADMIN_USER=admin
      - INFLUXDB_ADMIN_PASSWORD=influx
      - INFLUXDB_USER=telegraf
      - INFLUXDB_USER_PASSWORD=telegraf  
    start: always
```

***Puntos importantes:***

```
- environment: Aquí refeljamos todos los usuarios y passwords de Influx. Debemos respetar los que indiquemos aquí con los que hemos indicado en el apartado de Telegraf
```

*Info sobre la imagen: https://hub.docker.com/_/influxdb*

**GRAFANA:** Finalmente solo nos queda comentar la parte del servicio de grafana, donde podremos crear el dashboard con los datos que le ofrezca Influx. La parte de configuración del fichero docker-compose es esta:

```yaml
  grafana:
    container_name: grafana
    image: grafana/grafana
    networks:
      - tig_net    
    ports:
      - "3000:3000"
    volumes:
      - grafana_volume:/var/lib/grafana
    restart: always

```

*Info sobre la imagen: https://hub.docker.com/r/grafana/grafana*

Estas son las partes que intervienen y como las definimos en el fichero docker-compose.yml para que se lancen y den como resultado un stack compacto y aparte del resto de containers que podamos tener en Docker. Ahora lo implementamos de forma práctica:

> Nota: A partir de ahora todo debe de hacerse con sudo, con lo que recomiendo usar:
>
> ```bash
> sudo su
> ```

1. Crear la carpeta */home/user/docker/dc_tig*

   ```bash
   mkdir /home/user/docker/dc_tig
   ```

2. Crear el fichero de *docker-compose*

   ```bash
   cd /home/user/docker/dc_tig
   nano docker-compose.yml 
   ```

   y pegamos el código que hemos explicado arriba, que queda así:

   ```yaml
   version: "3.3"
   services:
     influxdb:
       container_name: influxdb
       image: influxdb
       networks:
         - tig_net    
       ports:
         - "8086:8086"
       volumes:
         - ./tig/data/influxdb:/var/lib/influxdb
       environment:
         - INFLUXDB_DB=telegraf
         - INFLUXDB_ADMIN_USER=admin
         - INFLUXDB_ADMIN_PASSWORD=influx
         - INFLUXDB_USER=telegraf
         - INFLUXDB_USER_PASSWORD=telegraf      
       restart: always
   
     grafana:
       container_name: grafana
       image: grafana/grafana
       networks:
         - tig_net    
       ports:
         - "3000:3000"
       volumes:
         - grafana_volume:/var/lib/grafana
       restart: always 
   
     mqtt:
       container_name: mqtt
       image: eclipse-mosquitto:latest
       networks:
         - tig_net    
       ports:
         - "1883:1883"
         - "9001:9001"
       user: "0"
       volumes:
         - mosquitto_volume:/mosquitto
       restart: always
   
     telegraf:
       container_name: telegraf
       image: telegraf
       networks:
         - tig_net    
       volumes:
         - ./tig/config/telegraf:/etc/telegraf:ro
         - /var/run/docker.sock:/var/run/docker.sock
       restart: always
       depends_on:
         - influxdb
         - mqtt
   
     chronograf:
       container_name: chronograf
       image: chronograf:latest
       ports:
         - "8888:8888"
       volumes:
         - "./chronograf:/var/lib/chronograf"
       networks:
         - tig_net
       
   networks:
       tig_net:
   
   volumes:
       grafana_volume:
       telegraf_volume:
       mosquitto_volume:
   ```

   > Nota: Hemos añadido la parte de *chronograf*, pero no es impresicindible. Es útil de todas formas y por eso lo incluimos.

3. Poner en marcha todos los servicios. Situándonos en la carpeta /home/user/docker/dc_tig ejecutaremos el comando:

   ```bash
   docker-compose up -d
   ```

   Si lo hemos hecho bien, empezará a descargarse las imágenes de cada servicio y al final las pondrá en marcha. Nos saldrá una imagen como la siguiente:

   #### Verificación

   -----------

   A partir de aquí, ya tenemos los servicios levantados y podemos acceder a cada uno de ellos:

   - **Grafana**: mediante un navegador accediendo a la IP o localhost:3000.

   - **Influx**: mediante el acceso directo al docker en cuestión arrancando el cliente de influx:

     ```bash
     docker exec -it influxdb influx
     ```

     Usando el comando *show databases;* podemos observar que ya se ha creado la base de datos para telegraf.

   - **Telegraf**: Este servicio tiene un poco más de misterio. Al levantarlo así, que es tal y como se recomienda en la documentación, no encuentra el fichero de configuración, con lo cual, hay que pararlo, copiarlo y volverlo a levantar:
     
     - parar de nuevo el docker-compose:
     
     ```bash
     docker-compose down
     ```
     
     - copiar el fichero telegraf.conf con la configuración que queremos a la carpeta */home/user/docker/dc_tig/tig/data/config/telegraf.conf* 
     
     - levantar de nuevo los servicios.
     
     ```bash
     docker-compose up -d
     ```
     
     Para saber si Telegraf se ha levantado correctamente, interrogaremos al log del mismo servicio, tal y como indican en la [documentación](https://hub.docker.com/_/telegraf) 
     
     ```bash
     docker logs -f telegraf
     ```

   - **MQTT**: podremos ver que el servicio de MQTT está levantado usando un cliente o tal y como hemos hecho anteriormente, revisando los logs del propio contenedor.

     ```bash
     docker logs -f mqtt
     ```

#### Puesta en marcha

----------

Ahora queda:

- Crear usuario de grafana

  Usuari admin inicial, contrasenya admin

- Crear la BBDD en IfluxDB

- Revisar con Chronograf que se reciben los datos

- Crear un dashboard en grafana

//CONTINUAR

*Imagen de portada creada por <a href='https://www.freepik.es/vectores/humo'>Vector de Humo creado por macrovector - www.freepik.es</a>

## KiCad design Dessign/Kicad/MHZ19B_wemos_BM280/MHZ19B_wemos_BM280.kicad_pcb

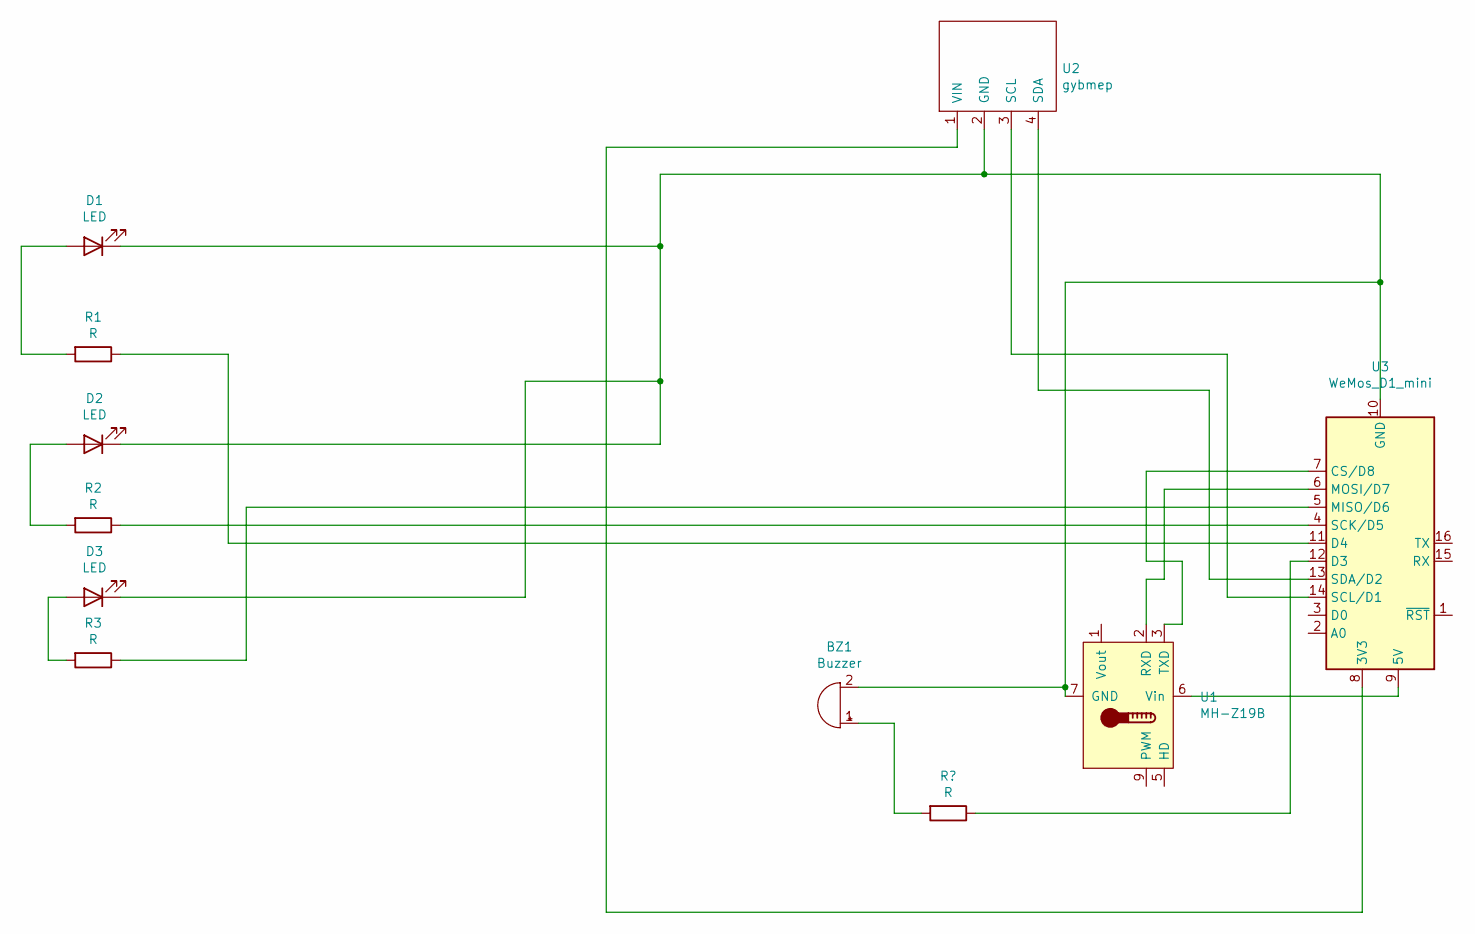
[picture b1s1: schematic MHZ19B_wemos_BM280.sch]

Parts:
BZ1: Buzzer; Buzzer_12x9.5RM7.6
D1, D2, D3: LED; LED_D5.0mm
R1, R2, R3: R; R_Axial_DIN0207_L6.3mm_D2.5mm_P10.16mm_Horizontal
U1: MH-Z19B; Winsen_MH-Z19B
U2: gybmep; GY-BME280
U3: WeMos_D1_mini; WEMOS_D1_mini_light

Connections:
unnamed: BZ1.2 (+), D1.1 (K), D2.1 (K), D3.1 (K), U1.7 (GND), U2.2 (GND), U3.10 (GND)
unnamed: D1.2 (A), R1.2
unnamed: D2.2 (A), R2.2
unnamed: D3.2 (A), R3.2
unnamed: R1.1, U3.11 (D4)
unnamed: R2.1, U3.4 (SCK/D5)
unnamed: R3.1, U3.5 (MISO/D6)
unnamed: U1.2 (RXD), U3.6 (MOSI/D7)
unnamed: U1.3 (TXD), U3.7 (CS/D8)
unnamed: U1.6 (Vin), U3.9 (5V)
unnamed: U2.1 (VIN), U3.8 (3V3)
unnamed: U2.3 (SCL), U3.14 (SCL/D1)
unnamed: U2.4 (SDA), U3.13 (SDA/D2)

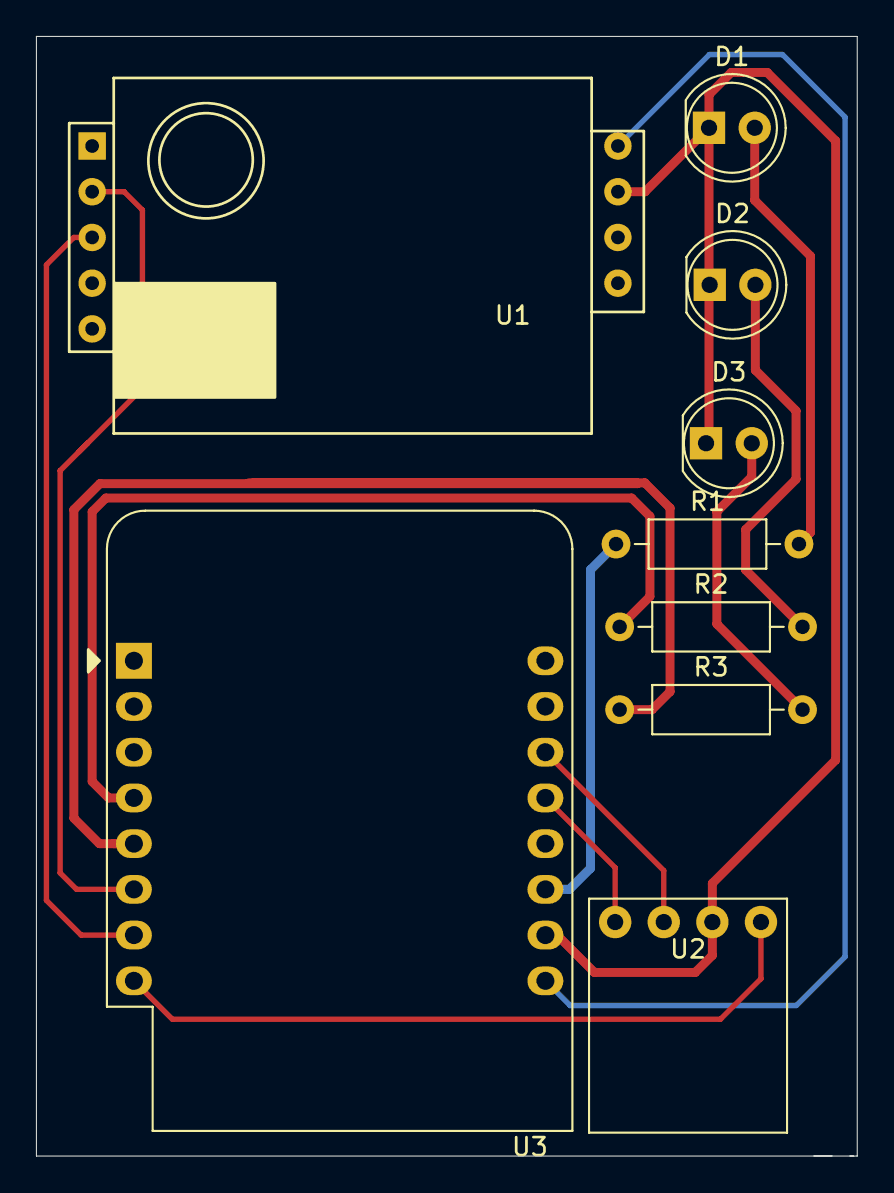
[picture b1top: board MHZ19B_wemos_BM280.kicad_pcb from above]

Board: 2 copper layers, 45.6 x 62.2 mm, 9 parts (0 on the bottom side), 13 nets.

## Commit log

2020-12-14 Create Arduino
2020-12-14 Rename CO2_thershold.h to Arduino/CO2_thershold.h
2020-12-14 Rename Config.h to Arduino/Config.h
2020-12-14 Rename MHZ19B_wemos_BM280.1.2.ino to Arduino/MHZ19B_wemos_BM280.1.2.ino
2020-12-14 Rename Wifi_credentials.h to Arduino/Wifi_credentials.h
2021-01-20 Rename README.md to README_old.md
2021-01-20 Rename README - SENSOR DE CO2.md to README.md
2021-01-24 Rename README.md to README1.md
